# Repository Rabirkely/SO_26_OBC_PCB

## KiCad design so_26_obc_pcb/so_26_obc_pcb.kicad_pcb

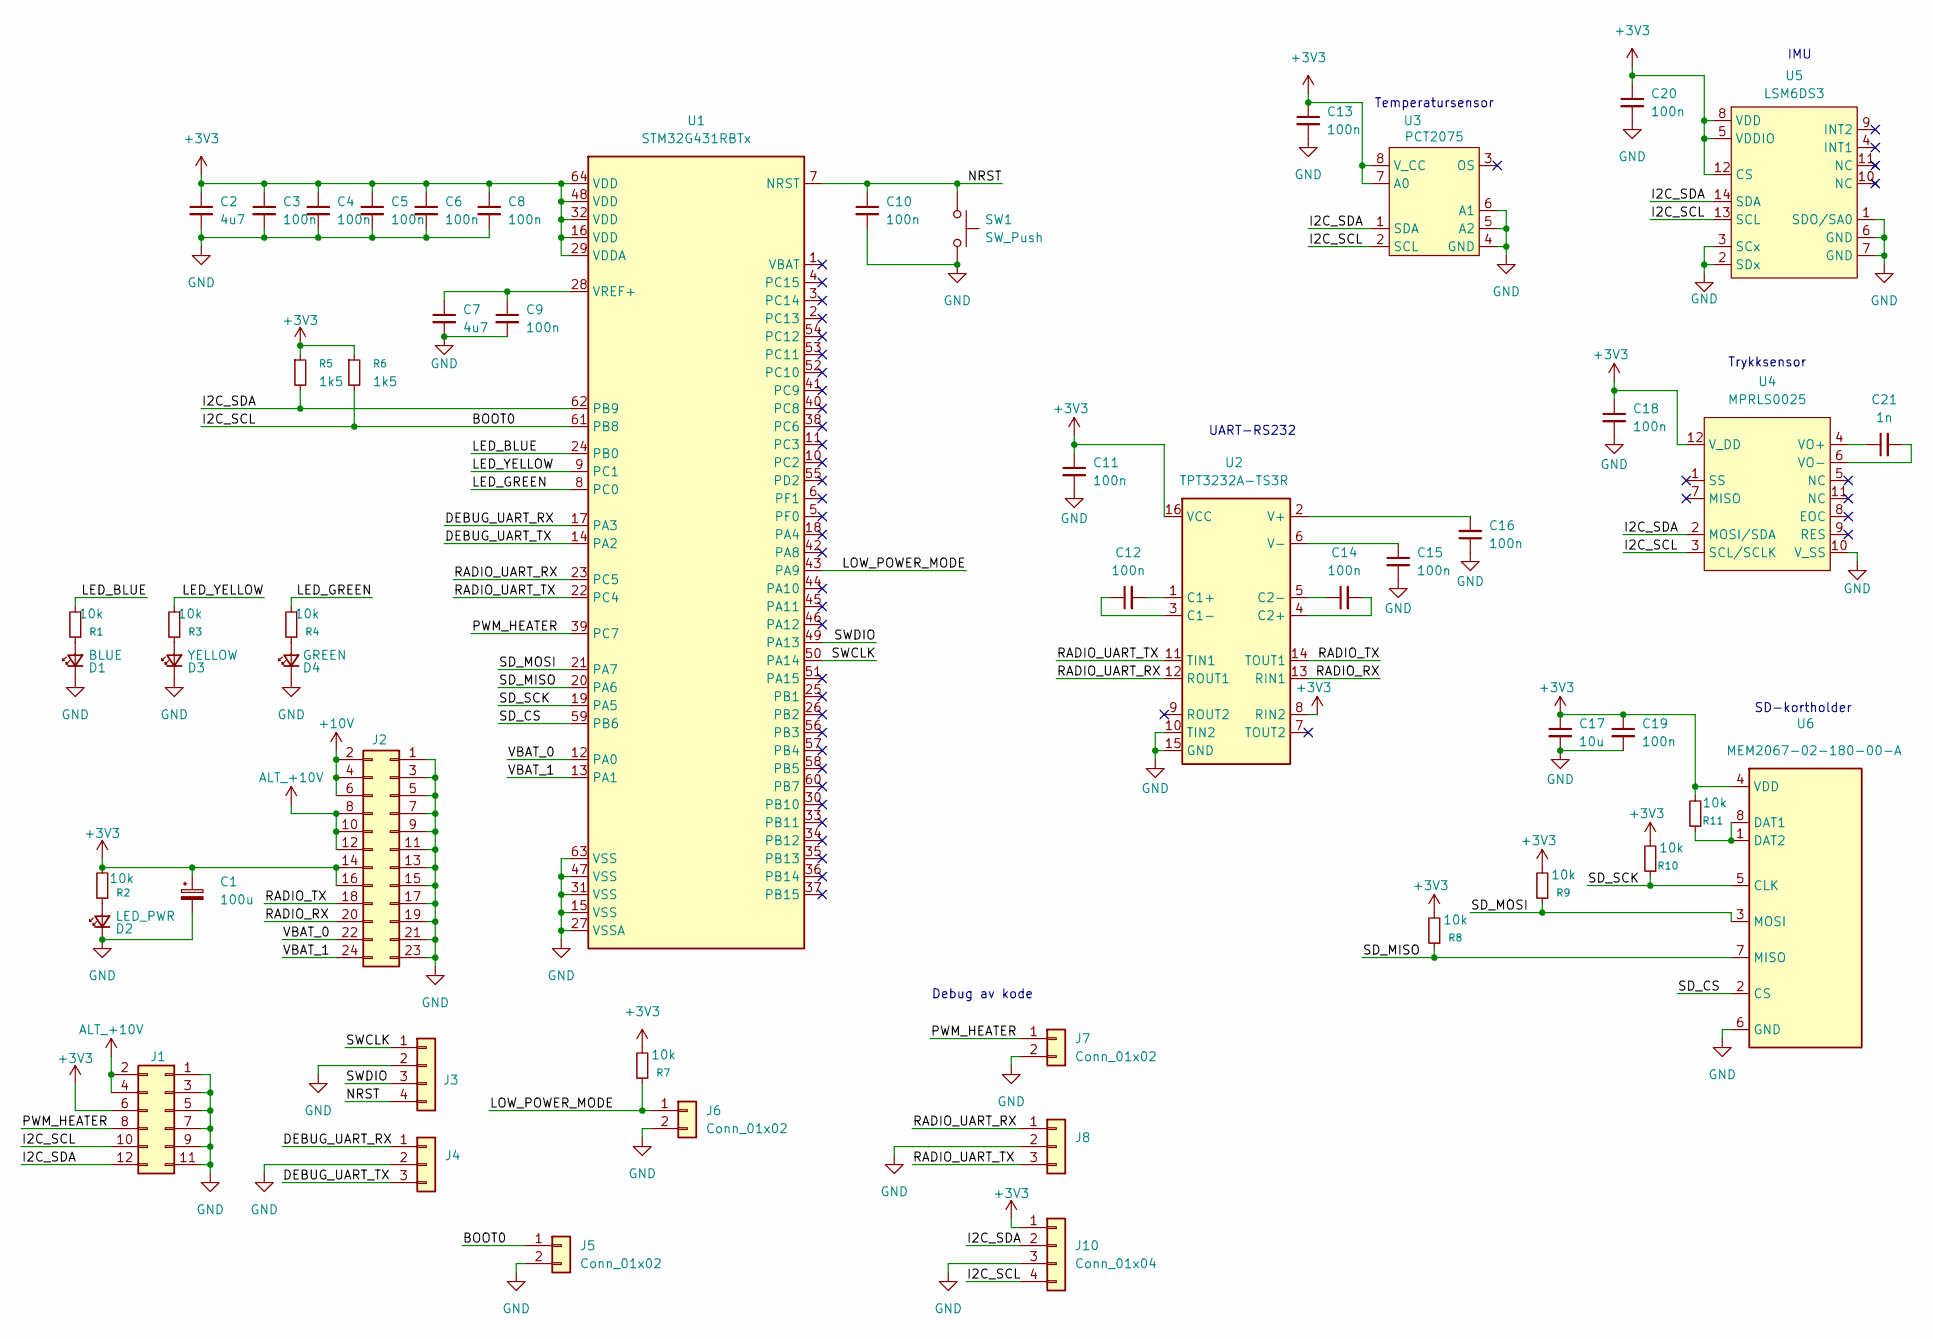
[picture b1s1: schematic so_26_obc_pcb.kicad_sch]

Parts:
C1: 100u; CP_Radial_D6.3mm_P2.50mm
C2, C7: 4u7; C_1206_3216Metric_Pad1.33x1.80mm_HandSolder
C3, C4, C5, C6, C8, C9, C10, C11, C12, C13, C14, C15, C16, C18, C19, C20: 100n; C_0805_2012Metric_Pad1.18x1.45mm_HandSolder
C17: 10u; C_1206_3216Metric_Pad1.33x1.80mm_HandSolder
C21: 1n; C_0805_2012Metric_Pad1.18x1.45mm_HandSolder
D1: BLUE; LED_0805_2012Metric_Pad1.15x1.40mm_HandSolder
D2: LED_PWR; LED_0805_2012Metric_Pad1.15x1.40mm_HandSolder
D3: YELLOW; LED_0805_2012Metric_Pad1.15x1.40mm_HandSolder
D4: GREEN; LED_0805_2012Metric_Pad1.15x1.40mm_HandSolder
J1: Conn_02x06_Odd_Even; PinSocket_2x06_P2.54mm_Vertical
J2: Conn_02x12_Odd_Even; PinSocket_2x12_P2.54mm_Vertical
J3, J10: Conn_01x04; PinHeader_1x04_P2.54mm_Vertical
J4, J8: Conn_01x03; PinHeader_1x03_P2.54mm_Vertical
J5, J6, J7: Conn_01x02; PinSocket_1x02_P2.54mm_Vertical
R1, R2, R3, R4, R7, R8, R9, R10, R11: 10k; R_0805_2012Metric_Pad1.20x1.40mm_HandSolder
R5, R6: 1k5; R_0805_2012Metric_Pad1.20x1.40mm_HandSolder
SW1: SW_Push; SW_PUSH_6mm
U1: STM32G431RBTx; LQFP-64_10x10mm_P0.5mm
U2: TPT3232A-TS3R; TSSOP-16_4.4x5mm_P0.65mm
U3: PCT2075; TSSOP-8_3x3mm_P0.65mm
U4: MPRLS0025; MPRLS0025PA00002A
U5: LSM6DS3; LGA-14_3x2.5mm_P0.5mm_LayoutBorder3x4y
U6: MEM2067-02-180-00-A

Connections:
+3V3: C1.1, C2.1, C3.1, C4.1, C5.1, C6.1, C8.1, C11.1, C13.1, C17.1, C18.1, C19.1, C20.1, J1.6, J2.14, J2.16, J10.1, R2.2, R5.1, R6.1, R7.2, R8.2, R9.2, R10.2, R11.2, U1.16 (VDD), U1.29 (VDDA), U1.32 (VDD), U1.48 (VDD), U1.64 (VDD), U2.8 (RIN2), U2.16 (VCC), U3.7 (A0), U3.8 (V_CC), U4.12 (V_DD), U5.5 (VDDIO), U5.8 (VDD), U5.12 (CS), U6.4 (VDD)
+10V: J2.2, J2.4, J2.6
/BOOT0: J1.10, J5.1, J10.4, R6.2, U1.61 (PB8), U3.2 (SCL), U4.3 (SCL/SCLK), U5.13 (SCL)
/DEBUG_UART_RX: J4.1, U1.17 (PA3)
/DEBUG_UART_TX: J4.3, U1.14 (PA2)
/I2C_SDA: J1.12, J10.2, R5.2, U1.62 (PB9), U3.1 (SDA), U4.2 (MOSI/SDA), U5.14 (SDA)
/LED_BLUE: R1.2, U1.24 (PB0)
/LED_GREEN: R4.2, U1.8 (PC0)
/LED_YELLOW: R3.2, U1.9 (PC1)
/LOW_POWER_MODE: J6.1, R7.1, U1.43 (PA9)
/NRST: C10.1, J3.4, SW1.1, U1.7 (NRST)
/PWM_HEATER: J1.8, J7.1, U1.39 (PC7)
/RADIO_RX: J2.20, U2.13 (RIN1)
/RADIO_TX: J2.18, U2.14 (TOUT1)
/RADIO_UART_RX: J8.1, U1.23 (PC5), U2.12 (ROUT1)
/RADIO_UART_TX: J8.3, U1.22 (PC4), U2.11 (TIN1)
/SD_CS: U1.59 (PB6), U6.2 (CS)
/SD_MISO: R8.1, U1.20 (PA6), U6.7 (MISO)
/SD_MOSI: R9.1, U1.21 (PA7), U6.3 (MOSI)
/SD_SCK: R10.1, U1.19 (PA5), U6.5 (CLK)
/SWCLK: J3.1, U1.50 (PA14)
/SWDIO: J3.3, U1.49 (PA13)
/VBAT_0: J2.22, U1.12 (PA0)
/VBAT_1: J2.24, U1.13 (PA1)
ALT_+10V: J1.2, J1.4, J2.8, J2.10, J2.12
GND: C1.2, C2.2, C3.2, C4.2, C5.2, C6.2, C7.2, C8.2, C9.2, C10.2, C11.2, C13.2, C15.2, C16.1, C17.2, C18.2, C19.2, C20.2, D1.1 (K), D2.1 (K), D3.1 (K), D4.1 (K), J1.1, J1.3, J1.5, J1.7, J1.9, J1.11, J2.1, J2.3, J2.5, J2.7, J2.9, J2.11, J2.13, J2.15, J2.17, J2.19, J2.21, J2.23, J3.2, J4.2, J5.2, J6.2, J7.2, J8.2, J10.3, SW1.2, U1.15 (VSS), U1.27 (VSSA), U1.31 (VSS), U1.47 (VSS), U1.63 (VSS), U2.10 (TIN2), U2.15 (GND), U3.4 (GND), U3.5 (A2), U3.6 (A1), U4.10 (V_SS), U5.1 (SDO/SA0), U5.2 (SDx), U5.3 (SCx), U5.6 (GND), U5.7 (GND), U6.6 (GND)
unnamed: D1.2 (A), R1.1
unnamed: D2.2 (A), R2.1
unnamed: D3.2 (A), R3.1
unnamed: D4.2 (A), R4.1
unnamed: C7.1, C9.1, U1.28 (VREF+)
unnamed: C12.2, U2.1 (C1+)
unnamed: C12.1, U2.3 (C1-)
unnamed: C14.2, U2.4 (C2+)
unnamed: C14.1, U2.5 (C2-)
unnamed: C16.2, U2.2 (V+)
unnamed: C15.1, U2.6 (V-)
unnamed: C21.1, U4.4 (VO+)
unnamed: C21.2, U4.6 (VO-)
unnamed: R11.1, U6.1 (DAT2), U6.8 (DAT1)

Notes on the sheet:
Trykksensor
Temperatursensor
UART-RS232
IMU
SD-kortholder
Debug av kode

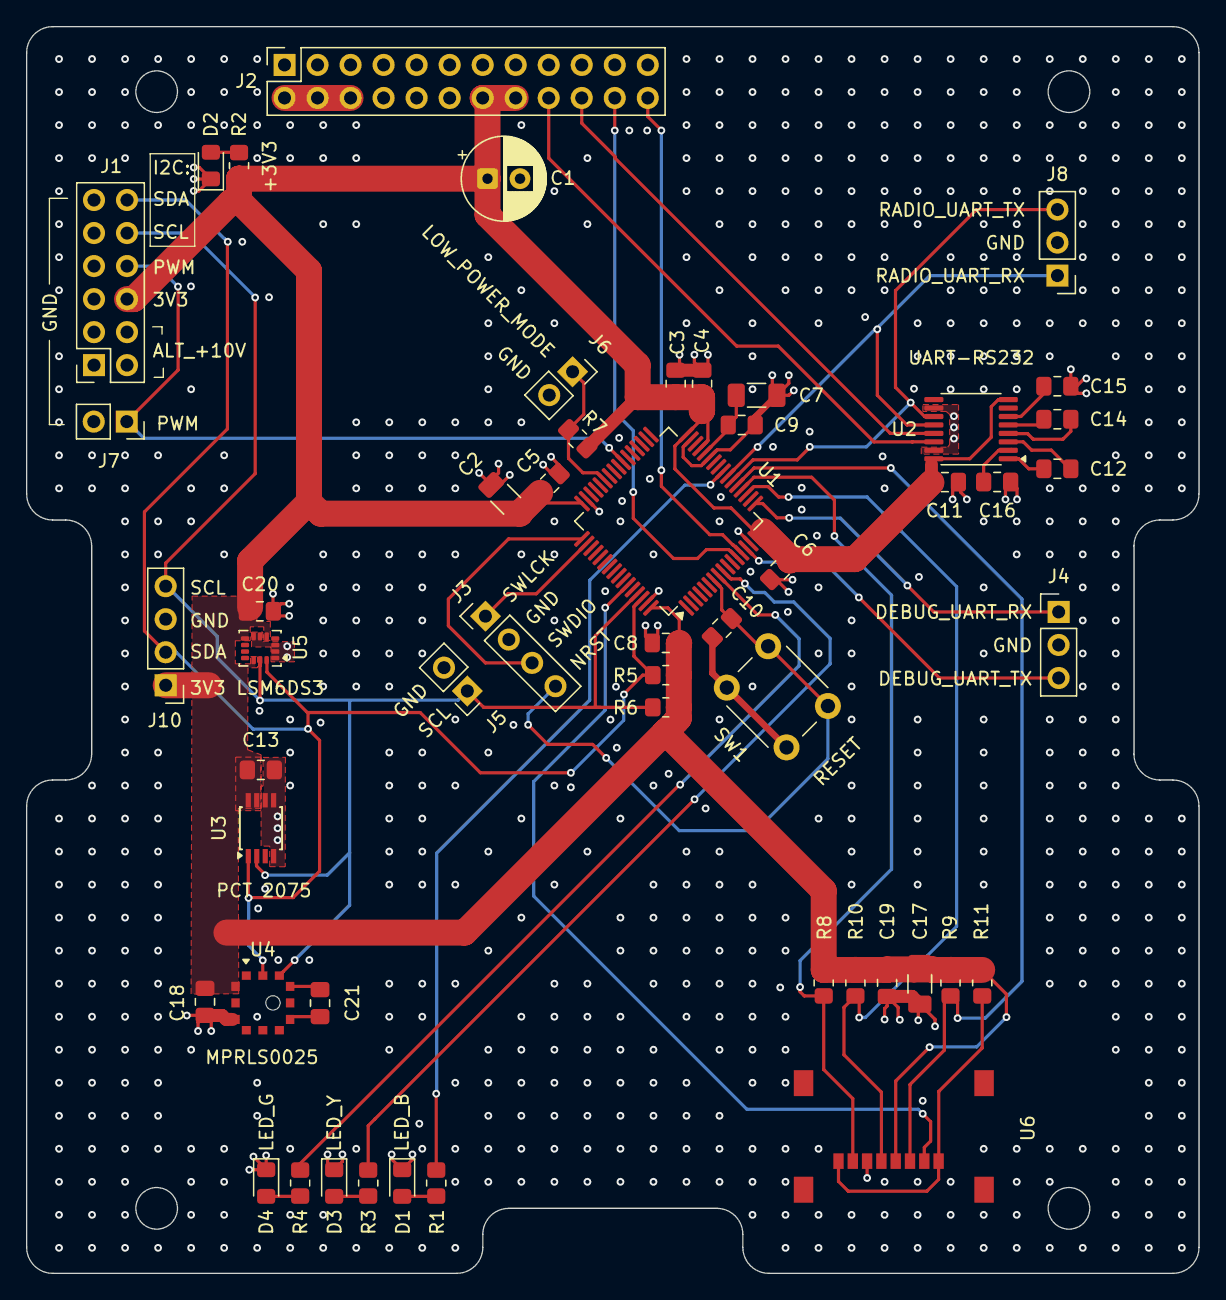
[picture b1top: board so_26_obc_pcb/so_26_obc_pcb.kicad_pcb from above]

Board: 4 copper layers, 90.2 x 95.9 mm, 52 parts (0 on the bottom side), 40 nets.

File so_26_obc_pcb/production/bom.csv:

Designator,Footprint,Quantity,Value,LCSC Part #
C1,CP_Radial_D6.3mm_P2.50mm,1,100u,
"C10, C11, C12, C13, C14, C15, C16, C18, C19, C20, C3, C4, C5, C6, C8, C9",0805,16,100n,
C17,1206,1,10u,
"C2, C7",1206,2,4u7,
C21,0805,1,1n,
D1,0805,1,BLUE,
D2,0805,1,LED_PWR,
D3,0805,1,YELLOW,
D4,0805,1,GREEN,
J1,PinSocket_2x12_P2.54mm_Vertical,1,Conn_02x12_Odd_Even,
"J10, J5, J9",PinSocket_1x02_P2.54mm_Vertical,3,Conn_01x02,
J2,PinSocket_2x06_P2.54mm_Vertical,1,Conn_02x06_Odd_Even,
J3,PinHeader_1x04_P2.54mm_Vertical,1,Conn_01x04,
"J4, J7, J8",PinHeader_1x03_P2.54mm_Vertical,3,Conn_01x03,
"R1, R10, R11, R2, R3, R4, R7, R8, R9",0805,9,10k,
"R5, R6",0805,2,1k5,
SW1,SW_PUSH_6mm,1,SW_Push,
U1,LQFP-64_10x10mm_P0.5mm,1,STM32G431RBTx,
U2,TSSOP-16_4.4x5mm_P0.65mm,1,TPT3232A-TS3R,
U3,TSSOP-8_3x3mm_P0.65mm,1,PCT2075,
U4,MPRLS0025PA00002A,1,MPRLS0025,
U5,LGA-14_3x2.5mm_P0.5mm_LayoutBorder3x4y,1,LSM6DS3,
U6,MEM2067-02-180-00-A,1,MEM2067-02-180-00-A,

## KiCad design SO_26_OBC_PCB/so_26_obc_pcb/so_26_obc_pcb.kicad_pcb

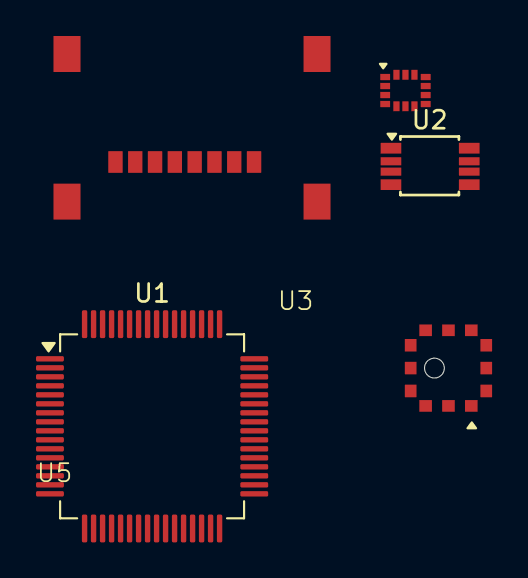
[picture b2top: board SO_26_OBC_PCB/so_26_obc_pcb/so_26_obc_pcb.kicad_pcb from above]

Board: 2 copper layers, 5 parts (0 on the bottom side), 9 nets, no tracks yet.

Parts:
U1: STM32G431RBTx; LQFP-64_10x10mm_P0.5mm
U2: PCT2075; TSSOP-8_3x3mm_P0.65mm
U3: MPRLS0025; MPRLS0025PA00002A
U4: LSM6DS3; LGA-14_3x2.5mm_P0.5mm_LayoutBorder3x4y
U5: MEM2067-02-180-00-A

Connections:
+3V3: U1.16 (VDD), U1.29 (VDDA), U1.32 (VDD), U1.48 (VDD), U1.64 (VDD), U3.12 (V_DD), U4.5 (VDDIO), U4.8 (VDD), U4.12 (CS), U5.4 (VDD)
/I2C_SCL: U1.61 (PB8), U2.2 (SCL), U3.3 (SCL/SCLK), U4.13 (SCL)
/I2C_SDA: U1.62 (PB9), U2.1 (SDA), U3.2 (MOSI/SDA), U4.14 (SDA)
/SD_CS: U1.59 (PB6), U5.2 (CS)
/SD_MISO: U1.20 (PA6), U5.3 (MOSI)
/SD_MOSI: U1.21 (PA7), U5.7 (MISO)
/SD_SCK: U1.19 (PA5), U5.5 (CLK)
GND: U1.15 (VSS), U1.27 (VSSA), U1.31 (VSS), U1.47 (VSS), U1.63 (VSS), U2.4 (GND), U3.10 (V_SS), U4.1 (SDO/SA0), U4.2 (SDx), U4.3 (SCx), U4.6 (GND), U4.7 (GND), U5.6 (GND)
unnamed: U5.1 (DAT2), U5.8 (DAT1)

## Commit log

2026-01-28 init commit
2026-01-28 schematic: updated title block
2026-02-05 Schematic: Added symbols + MCU setup
2026-02-07 schematic: added a lot, every ic basically
2026-02-08 checked by aj
    schematic
    - fixed mistakes
    pcb
    - added shape and stack
2026-02-08 checked by aj -> sch: fixed J2 missing connection
2026-02-08 Schematic: Added symbol for level shifter, updated footprint for pressure sensor
2026-02-08 Schematic: added low_power_mode
2026-02-08 PCB: changed settings to match specs from JCL
2026-02-08 Schematic: Updated level shifter symbol
2026-02-08 review by aj
    added max232cpe and other things
2026-02-09 changed back to old rs232 tranceiver
2026-02-09 Schematic: Added connector symbols for code debugging
2026-02-10 PCB: Placed components, did some routing
2026-02-10 PCB: routing v1
2026-02-10 PCB; screenshot
2026-02-11 PCB: Gave routing a couple of componentsone more try
2026-02-11 PCB: Routed before cleanup by AJ
2026-02-12 PCB: final routing + review
2026-02-12 stiching vias added
2026-02-12 added text
2026-02-22 Latest updates on rev1
2026-02-22 Rev2 beginning
2026-02-22 PCB: Placed components and IC's
2026-02-25 PCB: did some routing, almost done
2026-03-01 PCB: Finished routing, did DRC.
2026-03-01 PCB: Finished rev2, I think
2026-03-01 PCB: Final review rev2
